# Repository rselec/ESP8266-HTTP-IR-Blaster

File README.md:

# IR-Gateway

Ethernet (WiFi) to IR-Code Gateway to connect normal HiFi devices to the IoT.
Firmware is a fork of https://github.com/mdhiggins/ESP8266-HTTP-IR-Blaster and modified for a special Hardware.

Versions:
0.1 - development prototype on breadboard
0.2 - flying prototype with construction parts, transmitter only, longtime-test passed
0.3 - with custom back pcb and 3D case, wip

Kurze Übersicht der wichtigen Git-Befehle/Workflow:

1. bevor gearbeitet wird, Arbeitskopie aktualisieren:
	git pull
	
2. am Projekt arbeiten, nicht zu viel auf einmal
	
3. Änderungen überprüfen:
	git status
	
4. alle Änderungen zum Index hinzufügen:
	git add *
	
5. anschließend Änderungen im Index einchecken, mit kurzer Beschreibung:
	git commit -m "Commit-Nachricht"
	
6. jetzt noch die Änderungen zu bitbucket hochladen:
	git push

Release Versionen benennen (Tagging):

1. Versionsnummer in der main.c ändern (Schema "1.0")

2. compilieren und einen commit erstellen (wie oben)

3. den commit taggen: git tag -a v1.0 -m "release of version 1.0"

4. git push und git push --tags ausführen um den Tag auf den Server zu schieben

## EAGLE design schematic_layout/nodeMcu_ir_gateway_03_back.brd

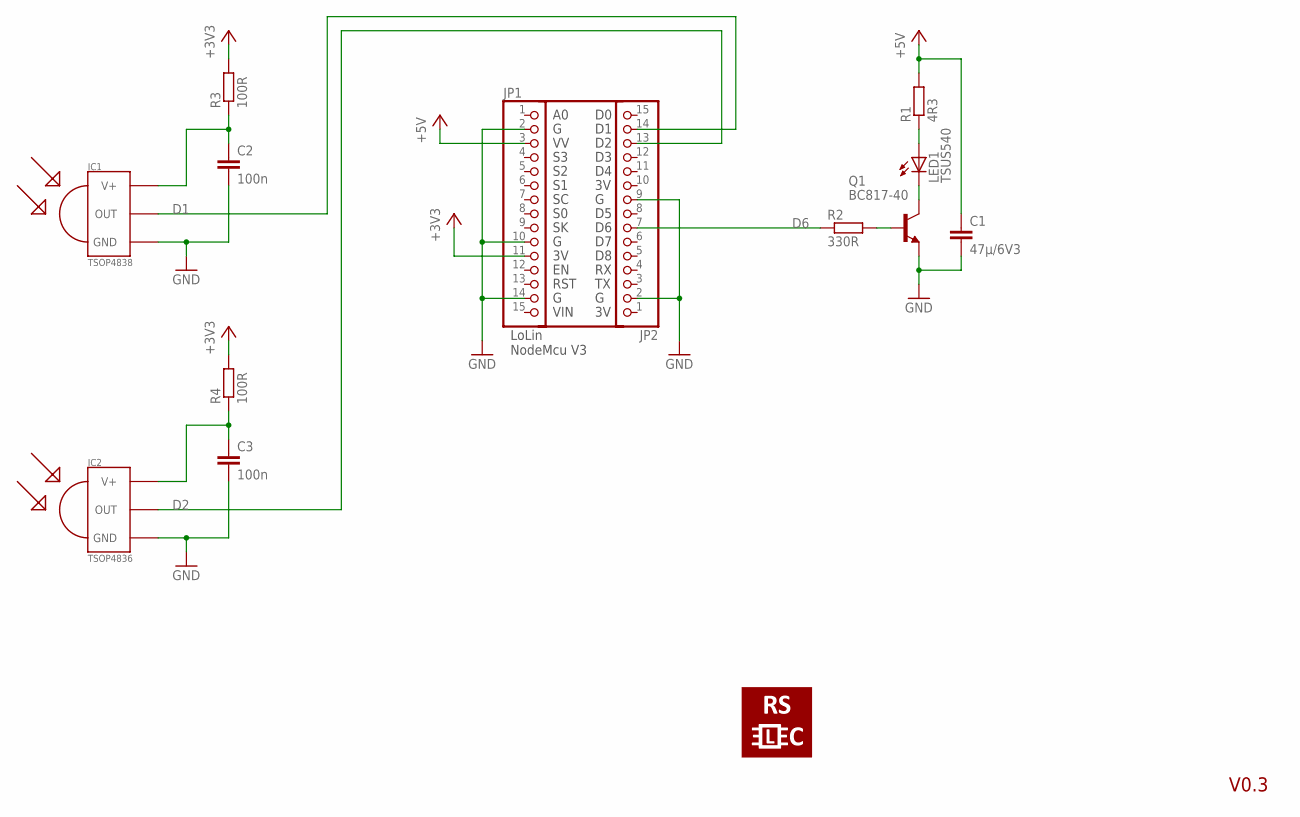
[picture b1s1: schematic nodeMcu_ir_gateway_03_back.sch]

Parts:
C1: 47µ/6V3; C1206
C2, C3: 100n; C0805
IC1: TSOP4838; TSOP18XX_H
IC2: TSOP4836; TSOP18XX_H
JP1, JP2: PINHD-1X15_2.54; 1X15
LED1: TSUS540; LED5MM
LOGO1: LOGO400N; LOGO_400N
Q1: BC817-40; SOT23-BEC
R1: 4R3; 0207/10
R2: 330R; R0805
R3, R4: 100R; R0805

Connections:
+3V3: JP1.11, R3.2, R4.2
+5V: C1.1, JP1.3, R1.2
D1: IC1.OUT, JP2.14
D2: IC2.OUT, JP2.13
D6: JP2.7, R2.1
GND: C1.2, C2.2, C3.2, IC1.GND, IC2.GND, JP1.2, JP1.10, JP1.14, JP2.2, JP2.9, Q1.E
unnamed: Q1.B, R2.2
unnamed: LED1.K (C), Q1.C
unnamed: LED1.A, R1.1
unnamed: C2.1, IC1.VCC (V+), R3.1
unnamed: C3.1, IC2.VCC (V+), R4.1

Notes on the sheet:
RST
VIN
LoLin NodeMcu V3
V0.3

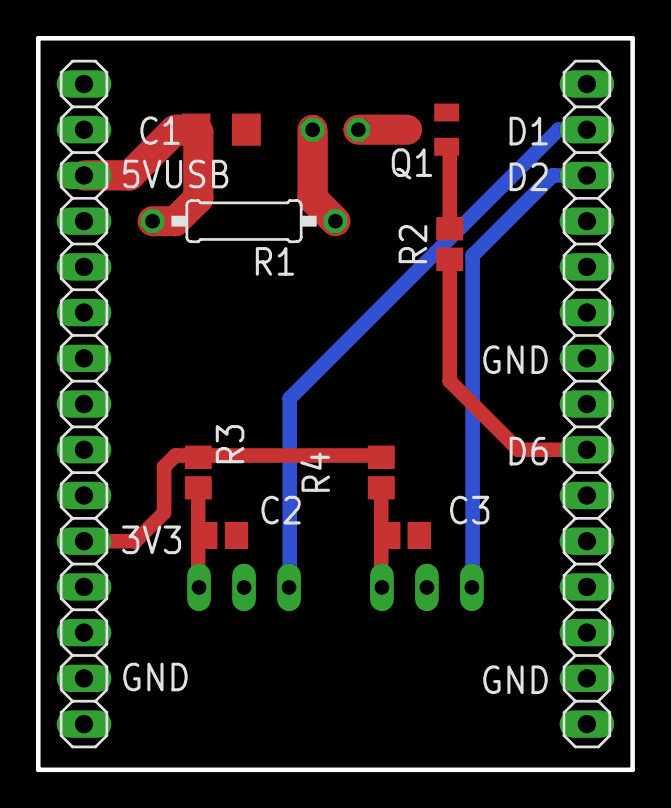
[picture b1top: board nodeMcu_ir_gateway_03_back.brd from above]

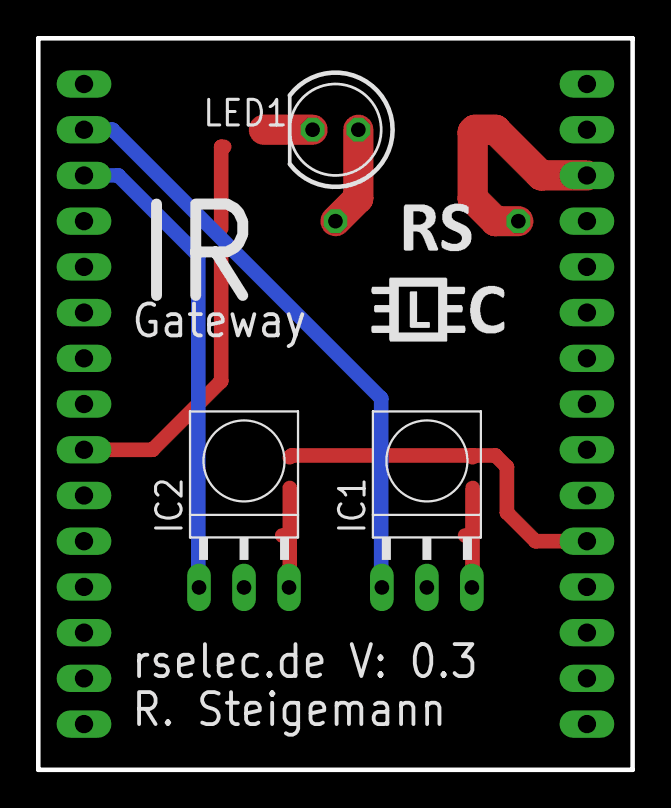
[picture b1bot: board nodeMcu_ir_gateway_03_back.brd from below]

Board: 2 copper layers, 33.0 x 40.6 mm, 14 parts (4 on the bottom side), 11 nets.

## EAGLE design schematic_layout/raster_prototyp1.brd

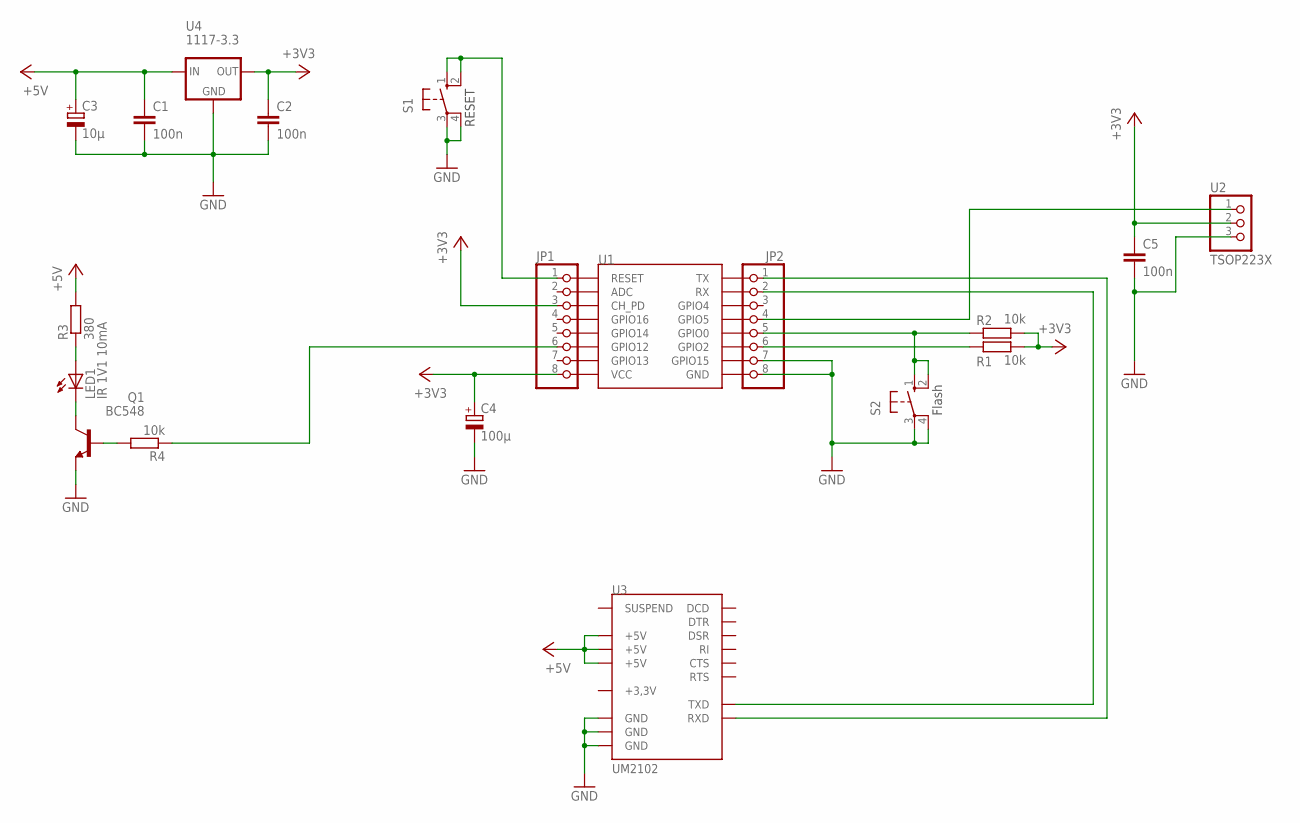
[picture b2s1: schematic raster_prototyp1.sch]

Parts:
C1, C2, C5: 100n; C0805
C3: 10µ; E2,5-5
C4: 100µ; E2,5-7
JP1, JP2: PINHD-1X8_2.54; 1X08
LED1: IR 1V1 10mA; LED5MM
Q1: BC548; TO92-EBC
R1, R2, R4: 10k; 0207/10
R3: 380; 0207/15
S1, S2: 10-XX; B3F-10XX
U1: ESP12SMD; ESP12-SMD
U2: TSOP223X; 1X03
U3: UM2102
U4: 1117-3.3; SOT223

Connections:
+3,3V: U3.ST2-11 (+3,3V)
+3V3: C2.1, C4.+, C5.1, JP1.3, JP1.8, R1.2, R2.2, U2.2, U4.2 (OUT)
+5V: C1.1, C3.+, R3.2, U3.ST1-3 (+5V), U3.ST2-9 (+5V), U3.ST3-7 (+5V), U4.3 (IN)
GND: C1.2, C2.2, C3.-, C4.-, C5.2, JP2.7, JP2.8, Q1.E, S1.3, S1.4 (P1), S2.3, S2.4 (P1), U2.3, U3.ST1-1 (GND), U3.ST2-7 (GND), U3.ST3-9 (GND), U4.1 (GND)
unnamed: JP2.4, U2.1
unnamed: JP2.6, R1.1
unnamed: LED1.A, R3.1
unnamed: JP1.1, S1.1 (S), S1.2 (S1)
unnamed: LED1.K (C), Q1.C
unnamed: JP2.5, R2.1, S2.1 (S), S2.2 (S1)
unnamed: Q1.B, R4.2
unnamed: JP1.6, R4.1
unnamed: JP2.1, U3.ST2-5 (RXD)
unnamed: JP2.2, U3.ST2-3 (TXD)

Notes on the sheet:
RESET
Flash

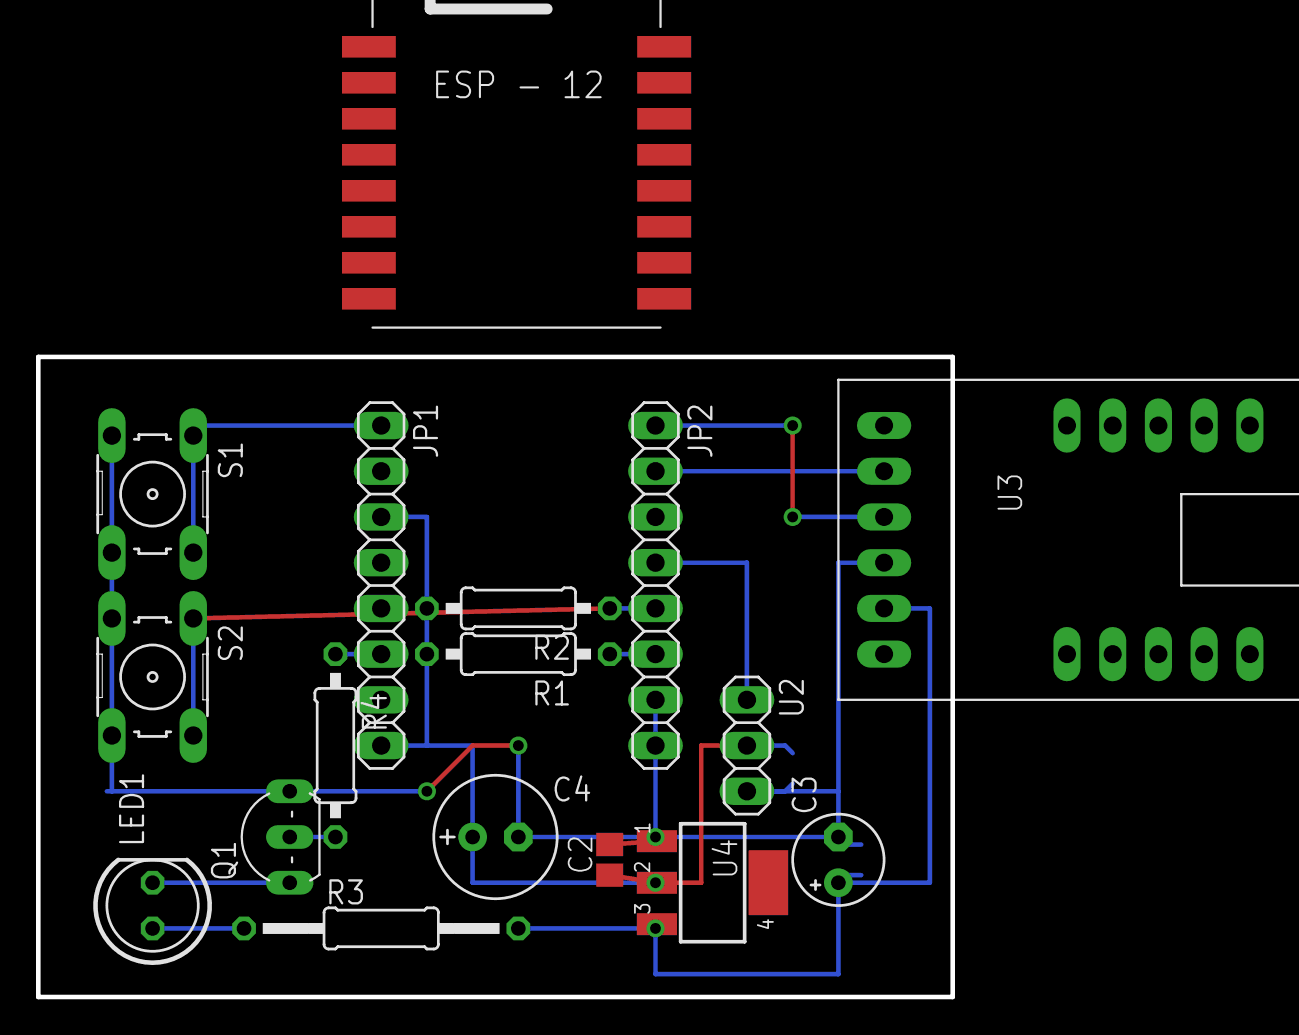
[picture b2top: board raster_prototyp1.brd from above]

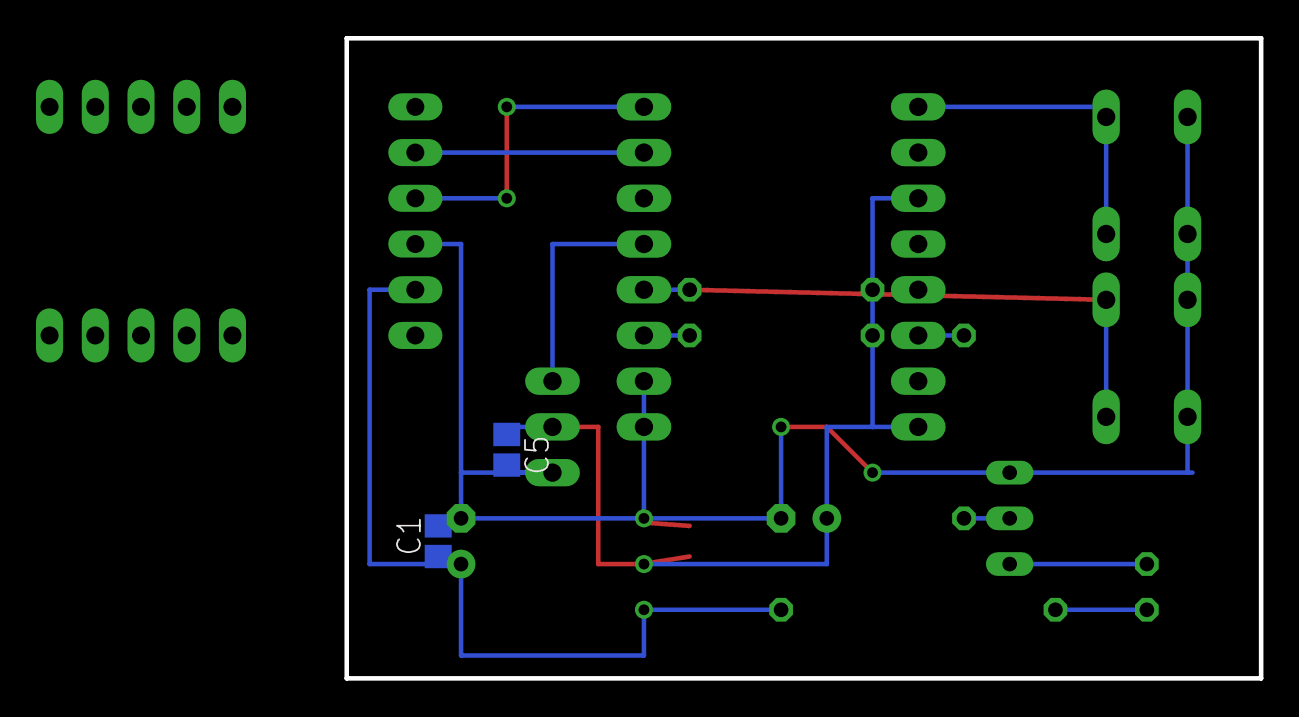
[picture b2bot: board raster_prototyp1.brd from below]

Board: 2 copper layers, 50.8 x 35.6 mm, 19 parts (2 on the bottom side), 13 nets.

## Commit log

2017-12-06 clear readme and adjusted code to IR-Gateway hardware, ready to test
2017-12-06 added project stuff
2017-12-06 added reset at config switch press
2017-12-24 added example NetIO project
2017-12-27 Fixed issues around panasonic address, works but mess with command (without addres) data (addres+command) and seperate address field isn't nice yet! Also fixed bug with stringcompare.
